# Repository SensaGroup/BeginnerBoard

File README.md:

# BeginnerBoard
BeginnerBoard designed by SENSA for beginners to get into electronics and programming.

## Top View

## Bottom View

## Specifications
The BeginnerBoard has all the necessary components to get started with Arduino from beginner to advanced level.

### Segments and components
- Power Segment
	- Input of 7V-25V
	- 7805 regulator (output current of 1.5A)
- Arduino NANO
	- One of the most popular Arduino boards with 5V logic
- Debug Segment
	- 3x LEDs
	- 2x Push Buttons or 1x Encoder 
	- 1x POT
- Relay Segment
	- Simple switch relay
	- Adjustable 5V/12V supply
- Stepper Segment
	- Powered by L293D using both drivers
	- Custom input voltage with diode protection 
- Dual Motor Segment
	- Powered by L293D
	- Custon input voltage or Input of 7V-25V from Power Segment
- Pinout for I2C

## Sponsored by AISLER
### Develop and manufacture your own premium boards at [aisler.net](https://aisler.net/)

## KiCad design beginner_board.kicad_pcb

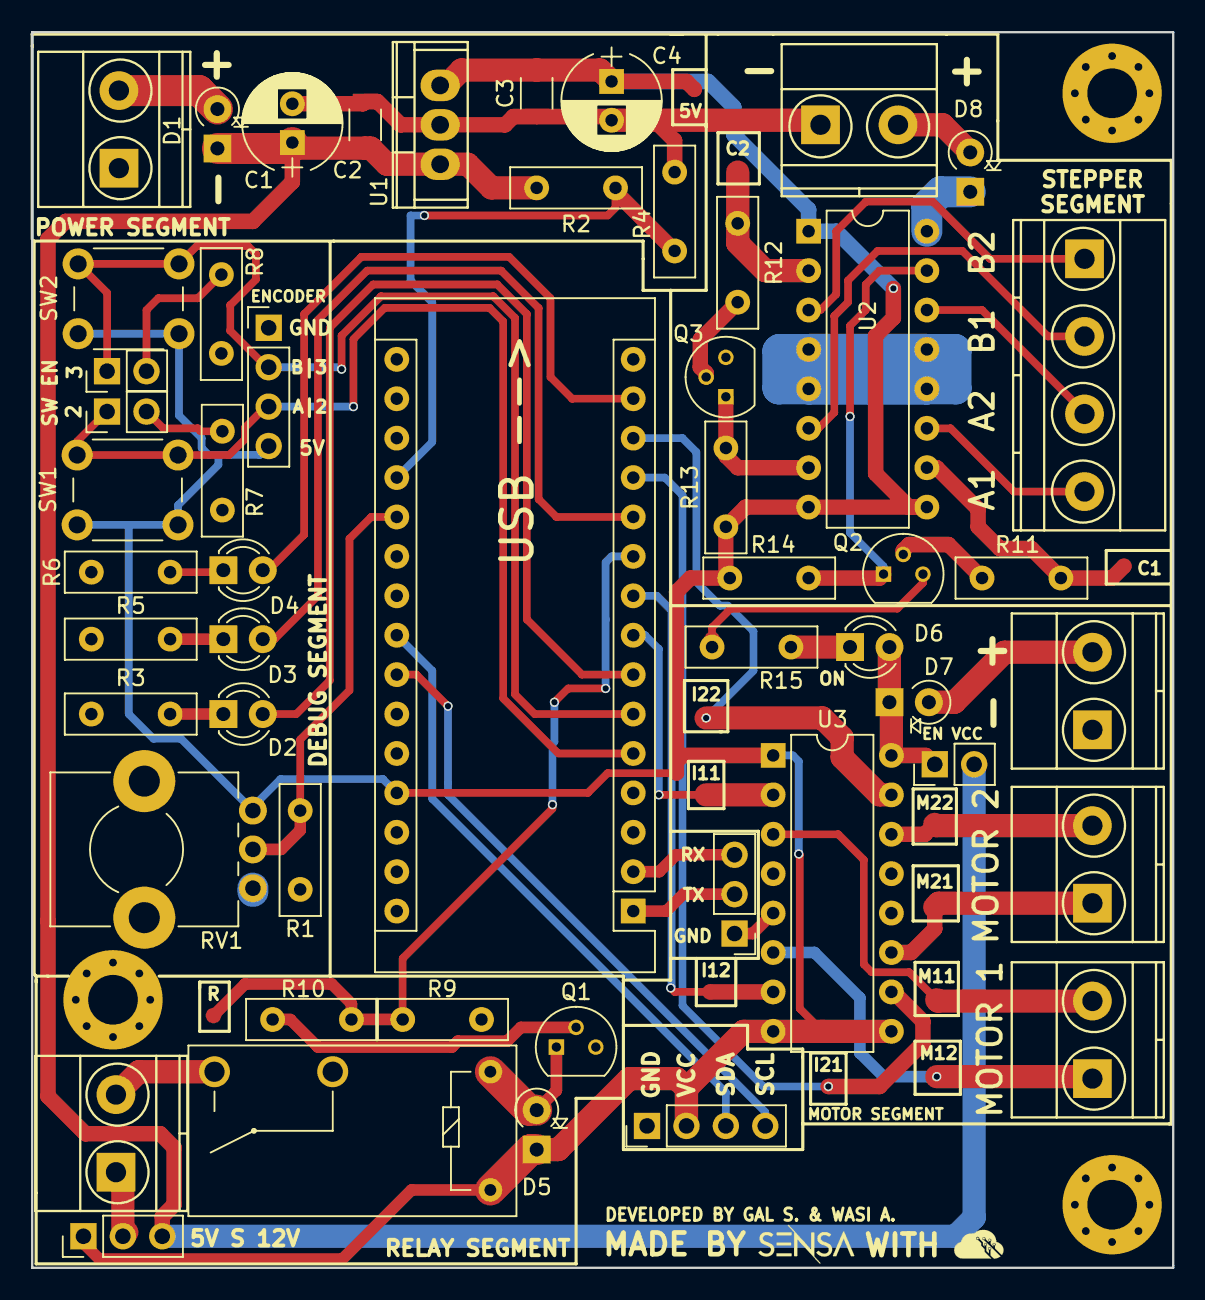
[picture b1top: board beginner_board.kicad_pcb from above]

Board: 2 copper layers, 73.5 x 79.6 mm, 67 parts (0 on the bottom side), 48 nets.

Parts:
A1: Arduino_Nano_v3.x; Arduino_Nano
C1, C4: CP; CP_Radial_D6.3mm_P2.50mm
C2, C3: C; C_1206
D1, D5, D7, D8: D; D_A-405_P2.54mm_Vertical_KathodeUp
D2, D3, D4, D6: LED; LED_D3.0mm
J1: I2C_STANDARD; Pin_Header_Straight_1x04_Pitch2.54mm
J2, J4, J6, J7, J8, J9: Screw_Terminal_01x02; TerminalBlock_Phoenix_MKDS1.5-2pol
J3, J11: Conn_01x03; Pin_Header_Straight_1x03_Pitch2.54mm
J5: Screw_Terminal_01x04; TerminalBlock_Phoenix_MKDS1.5-4pol
J10: Conn_01x04; Pin_Header_Straight_1x04_Pitch2.54mm
J12, J13, J14: Conn_01x02; Pin_Header_Straight_1x02_Pitch2.54mm
K1: G5Q-1A; Relay_SPST_OMRON-G5Q
MK1, MK2, MK4: Mounting_Hole; MountingHole_3.2mm_M3_Pad_Via
Q1, Q2, Q3: BC547; TO-92_Molded_Narrow
R1, R2, R7, R8, R9, R13, R14: 10K; R_Box_L8.4mm_W2.5mm_P5.08mm
R3, R4, R5, R6, R10, R11, R12, R15: 1K; R_Box_L8.4mm_W2.5mm_P5.08mm
RV1: POT; Potentiometer_Alps_RK09K_Horizontal
SW1, SW2: SW_Push; SW_PUSH_6mm
TP1, TP2, TP3, TP4, TP5, TP6, TP7, TP8, TP9, TP10, TP11, TP12: TEST; FIDUCIAL-1X2
U1: L7805; TO-220
U2, U3: L293D; DIP-16_W7.62mm

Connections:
+5V: A1.27, C3.1, C4.1, D5.1, J1.2, J3.1, J10.4, K1.5, R13.1, R14.1, RV1.1, SW1.1, SW2.1, TP1.1, U1.3, U2.1, U2.8, U2.9, U3.1, U3.8, U3.9
+12V: C1.1, C2.1, D1.1, J3.3, J12.2, R2.2, U1.1
A0: A1.19, R2.1, R4.2
A1: A1.20, R1.2, RV1.2
A4: A1.23, J1.3
A5: A1.24, J1.4
D0: A1.2, J11.3
D1: A1.1, J11.2
D2: A1.5, J10.3, J13.1, SW1.2
D3: A1.6, J10.2, J14.1, SW2.2
D4: A1.7, D2.2
D5: A1.8, TP11.1, U3.2
D6: A1.9, TP9.1, U3.7
D7: A1.10, R9.1, R10.2, TP2.1
D8: A1.11, D3.2
D9: A1.12, TP7.1, U3.10
D10: A1.13, TP5.1, U3.15
D11: A1.14, D4.2
GND: A1.4, A1.29, C1.2, C2.2, C3.2, C4.2, J1.1, J2.1, J6.1, J9.1, J10.1, J11.1, K1.2, Q1.3, Q2.3, Q3.3, R1.1, R3.1, R4.1, R5.1, R6.1, R7.1, R8.1, R9.2, R15.2, RV1.3, U1.2, U2.4, U2.5, U2.12, U2.13, U3.4, U3.5, U3.12, U3.13
MOTOR_PWR: D6.2, D7.1, J12.1, U3.16
M_O_11: J7.2, TP12.1, U3.3
M_O_12: J7.1, TP10.1, U3.6
M_O_21: J8.1, TP8.1, U3.11
M_O_22: J8.2, TP6.1, U3.14
unnamed: D1.2, J2.2
unnamed: D2.1, R3.2
unnamed: D3.1, R5.2
unnamed: D4.1, R6.2
unnamed: D5.2, K1.1, Q1.1
unnamed: D6.1, R15.1
unnamed: D7.2, J6.2
unnamed: D8.2, J9.2
unnamed: J3.2, J4.1
unnamed: J4.2, K1.3
unnamed: J5.1, U2.3
unnamed: J5.2, U2.6
unnamed: J5.3, U2.14
unnamed: J5.4, U2.11
unnamed: J13.2, R7.2
unnamed: J14.2, R8.2
unnamed: Q1.2, R10.1
unnamed: Q2.1, R14.2, U2.15
unnamed: Q2.2, R11.2
unnamed: Q3.1, R13.2, U2.7
unnamed: Q3.2, R12.2
STEPPER_PWR: D8.1, U2.16
STP_CON1: R12.1, TP3.1, U2.2
STP_CON2: R11.1, TP4.1, U2.10

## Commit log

2018-07-15 Added files and images
2018-07-15 Added pdfs
2018-07-25 sponsored*
2018-09-10 DEV for download
2018-09-19 new design with smd
